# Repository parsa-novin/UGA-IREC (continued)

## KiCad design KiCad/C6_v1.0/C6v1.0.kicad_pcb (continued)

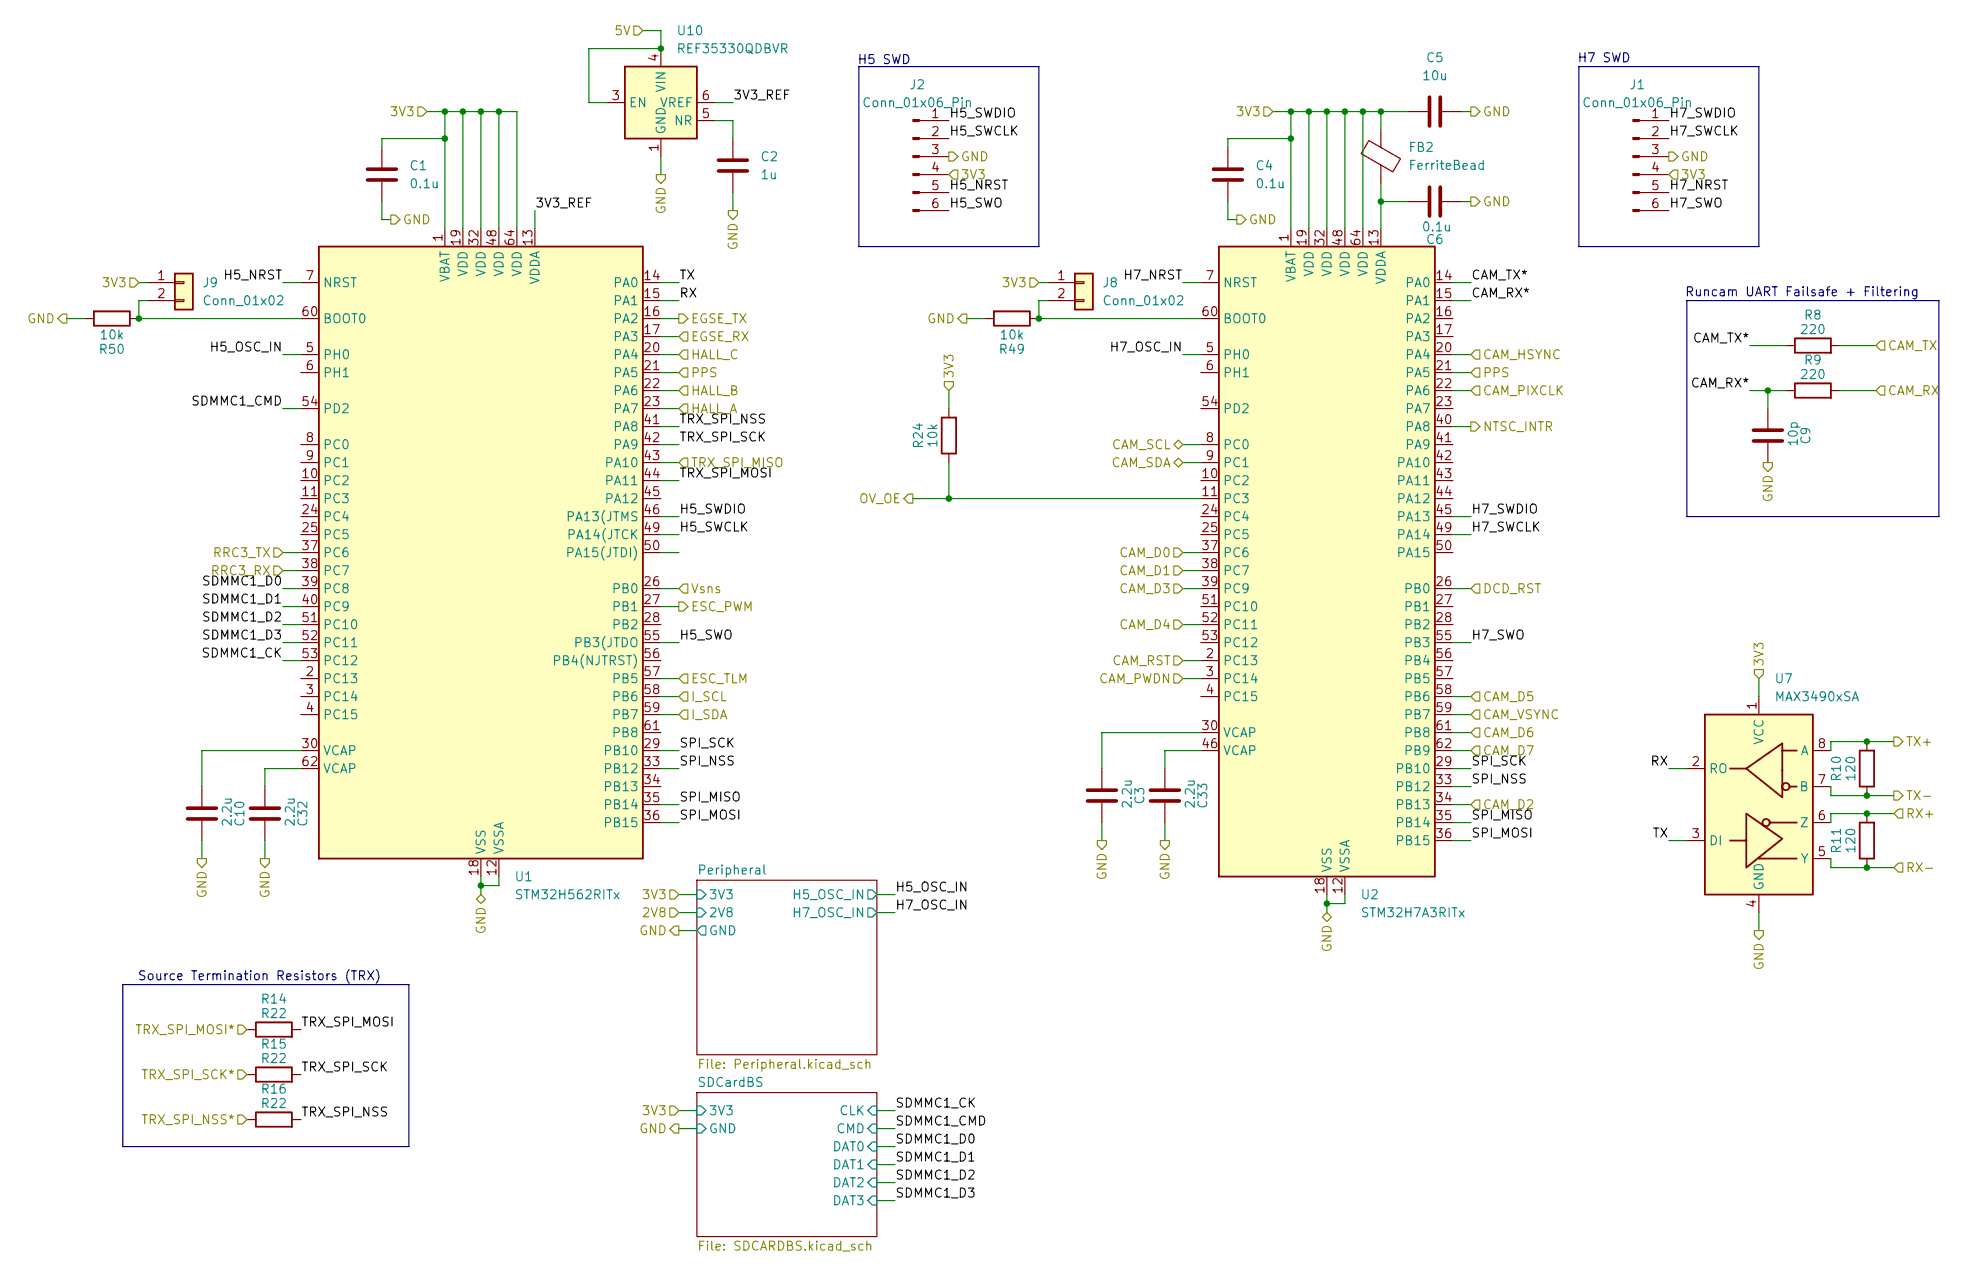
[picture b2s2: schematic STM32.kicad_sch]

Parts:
C1, C4, C6: 0.1u; C_0402_1005Metric_Pad0.74x0.62mm_HandSolder
C2: 1u; C_0402_1005Metric_Pad0.74x0.62mm_HandSolder
C3, C10, C32, C33: 2.2u; C_0402_1005Metric_Pad0.74x0.62mm_HandSolder
C5: 10u; C_0402_1005Metric_Pad0.74x0.62mm_HandSolder
C9: 10p; C_0402_1005Metric_Pad0.74x0.62mm_HandSolder
FB2: FerriteBead; R_0805_2012Metric
J1, J2: Conn_01x06_Pin; PinHeader_1x06_P2.54mm_Vertical
J8, J9: Conn_01x02; PinHeader_1x02_P2.54mm_Vertical
R8, R9: 220; R_0402_1005Metric_Pad0.72x0.64mm_HandSolder
R10, R11: 120; R_0402_1005Metric_Pad0.72x0.64mm_HandSolder
R14, R15, R16: R22; R_0402_1005Metric_Pad0.72x0.64mm_HandSolder
R24, R49, R50: 10k; R_0402_1005Metric_Pad0.72x0.64mm_HandSolder
U1: STM32H562RITx; LQFP-64_10x10mm_P0.5mm
U2: STM32H7A3RITx; LQFP-64_10x10mm_P0.5mm
U7: MAX3490xSA; SOIC-8_3.9x4.9mm_P1.27mm
U10: REF35330QDBVR; SOT-23-6

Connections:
/3V3: C1.2, C4.2, C5.2, FB2.1, J1.4, J2.4, J8.1, J9.1, R24.2, U1.1 (VBAT), U1.19 (VDD), U1.32 (VDD), U1.48 (VDD), U1.64 (VDD), U2.1 (VBAT), U2.19 (VDD), U2.32 (VDD), U2.48 (VDD), U2.64 (VDD), U7.1 (VCC); also elsewhere on the board
/5V: U10.3 (EN), U10.4 (VIN); also elsewhere on the board
/CAM_D0*: U2.37 (PC6); also elsewhere on the board
/CAM_D1*: U2.38 (PC7); also elsewhere on the board
/CAM_D2*: U2.34 (PB13); also elsewhere on the board
/CAM_D3*: U2.39 (PC9); also elsewhere on the board
/CAM_D4*: U2.52 (PC11); also elsewhere on the board
/CAM_D5*: U2.58 (PB6); also elsewhere on the board
/CAM_D6*: U2.61 (PB8); also elsewhere on the board
/CAM_D7*: U2.62 (PB9); also elsewhere on the board
/CAM_HSYNC*: U2.20 (PA4); also elsewhere on the board
/CAM_PCLK*: U2.22 (PA6); also elsewhere on the board
/CAM_PWDN*: U2.3 (PC14); also elsewhere on the board
/CAM_S: R24.1, U2.11 (PC3); also elsewhere on the board
/CAM_SCL: U2.8 (PC0); also elsewhere on the board
/CAM_SDA: U2.9 (PC1); also elsewhere on the board
/CAM_VSYNC*: U2.59 (PB7); also elsewhere on the board
/DCD_RST: U2.26 (PB0); also elsewhere on the board
/EGSE_RX: U1.17 (PA3); also elsewhere on the board
/EGSE_TX: U1.16 (PA2); also elsewhere on the board
/ESC_PWM: U1.27 (PB1); also elsewhere on the board
/ESC_TLM: U1.57 (PB5); also elsewhere on the board
/HALL_A: U1.23 (PA7); also elsewhere on the board
/HALL_B: U1.22 (PA6); also elsewhere on the board
/HALL_C: U1.20 (PA4); also elsewhere on the board
/I_SCL: U1.58 (PB6); also elsewhere on the board
/I_SDA: U1.59 (PB7); also elsewhere on the board
/NTSC_INTR: U2.40 (PA8); also elsewhere on the board
/OV_RST: U2.2 (PC13); also elsewhere on the board
/PPS: U1.21 (PA5), U2.21 (PA5); also elsewhere on the board
/RRC3_RX: U1.38 (PC7); also elsewhere on the board
/RRC3_TX: U1.37 (PC6); also elsewhere on the board
/RS422_RX+: R11.2, U7.6 (Z); also elsewhere on the board
/RS422_RX-: R11.1, U7.5 (Y); also elsewhere on the board
/RS422_TX+: R10.2, U7.8 (A); also elsewhere on the board
/RS422_TX-: R10.1, U7.7 (B); also elsewhere on the board
/SPLIT_RX: R9.2; also elsewhere on the board
/SPLIT_TX: R8.2; also elsewhere on the board
/STM32/3V3_REF: U1.13 (VDDA), U10.6 (VREF)
/STM32/CAM_RX*: C9.1, R9.1, U2.15 (PA1)
/STM32/CAM_TX*: R8.1, U2.14 (PA0)
/STM32/H5_NRST: J2.5, U1.7 (NRST)
/STM32/H5_OSC_IN: U1.5 (PH0); also elsewhere on the board
/STM32/H5_SWCLK: J2.2, U1.49 (PA14(JTCK)
/STM32/H5_SWDIO: J2.1, U1.46 (PA13(JTMS)
/STM32/H5_SWO: J2.6, U1.55 (PB3(JTDO)
/STM32/H7_NRST: J1.5, U2.7 (NRST)
/STM32/H7_OSC_IN: U2.5 (PH0); also elsewhere on the board
/STM32/H7_SWCLK: J1.2, U2.49 (PA14)
/STM32/H7_SWDIO: J1.1, U2.45 (PA13)
/STM32/H7_SWO: J1.6, U2.55 (PB3)
/STM32/RX: U1.15 (PA1), U7.2 (RO)
/STM32/SDMMC1_CK: U1.53 (PC12); also elsewhere on the board
/STM32/SDMMC1_CMD: U1.54 (PD2); also elsewhere on the board
/STM32/SDMMC1_D0: U1.39 (PC8); also elsewhere on the board
/STM32/SDMMC1_D1: U1.40 (PC9); also elsewhere on the board
/STM32/SDMMC1_D2: U1.51 (PC10); also elsewhere on the board
/STM32/SDMMC1_D3: U1.52 (PC11); also elsewhere on the board
/STM32/SPI_MISO: U1.35 (PB14), U2.35 (PB14)
/STM32/SPI_MOSI: U1.36 (PB15), U2.36 (PB15)
/STM32/SPI_NSS: U1.33 (PB12), U2.33 (PB12)
/STM32/SPI_SCK: U1.29 (PB10), U2.29 (PB10)
/STM32/TRX_SPI_MOSI: R14.2, U1.44 (PA11)
/STM32/TRX_SPI_NSS: R16.2, U1.41 (PA8)
/STM32/TRX_SPI_SCK: R15.2, U1.42 (PA9)
/STM32/TX: U1.14 (PA0), U7.3 (DI)
/TRX_MISO: U1.43 (PA10); also elsewhere on the board
/TRX_MOSI: R14.1; also elsewhere on the board
/TRX_NSS: R16.1; also elsewhere on the board
/TRX_SCK: R15.1; also elsewhere on the board
/Vsns: U1.26 (PB0); also elsewhere on the board
GND: C1.1, C2.1, C3.2, C4.1, C5.1, C6.1, C9.2, C10.2, C32.2, C33.2, J1.3, J2.3, R49.2, R50.2, U1.12 (VSSA), U1.18 (VSS), U1.31 (VSS), U1.47 (VSS), U1.63 (VSS), U2.12 (VSSA), U2.18 (VSS), U2.31 (VSS), U2.47 (VSS), U2.63 (VSS), U7.4 (GND), U10.1 (GND), U10.2 (GND); also elsewhere on the board
unnamed: C3.1, U2.30 (VCAP)
unnamed: C10.1, U1.30 (VCAP)
unnamed: C32.1, U1.62 (VCAP)
unnamed: C33.1, U2.46 (VCAP)
unnamed: J8.2, R49.1, U2.60 (BOOT0)
unnamed: J9.2, R50.1, U1.60 (BOOT0)
unnamed: C6.2, FB2.2, U2.13 (VDDA)
unnamed: C2.2, U10.5 (NR)

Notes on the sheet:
H7 SWD
Runcam UART Failsafe + Filtering
H5 SWD
Source Termination Resistors (TRX)

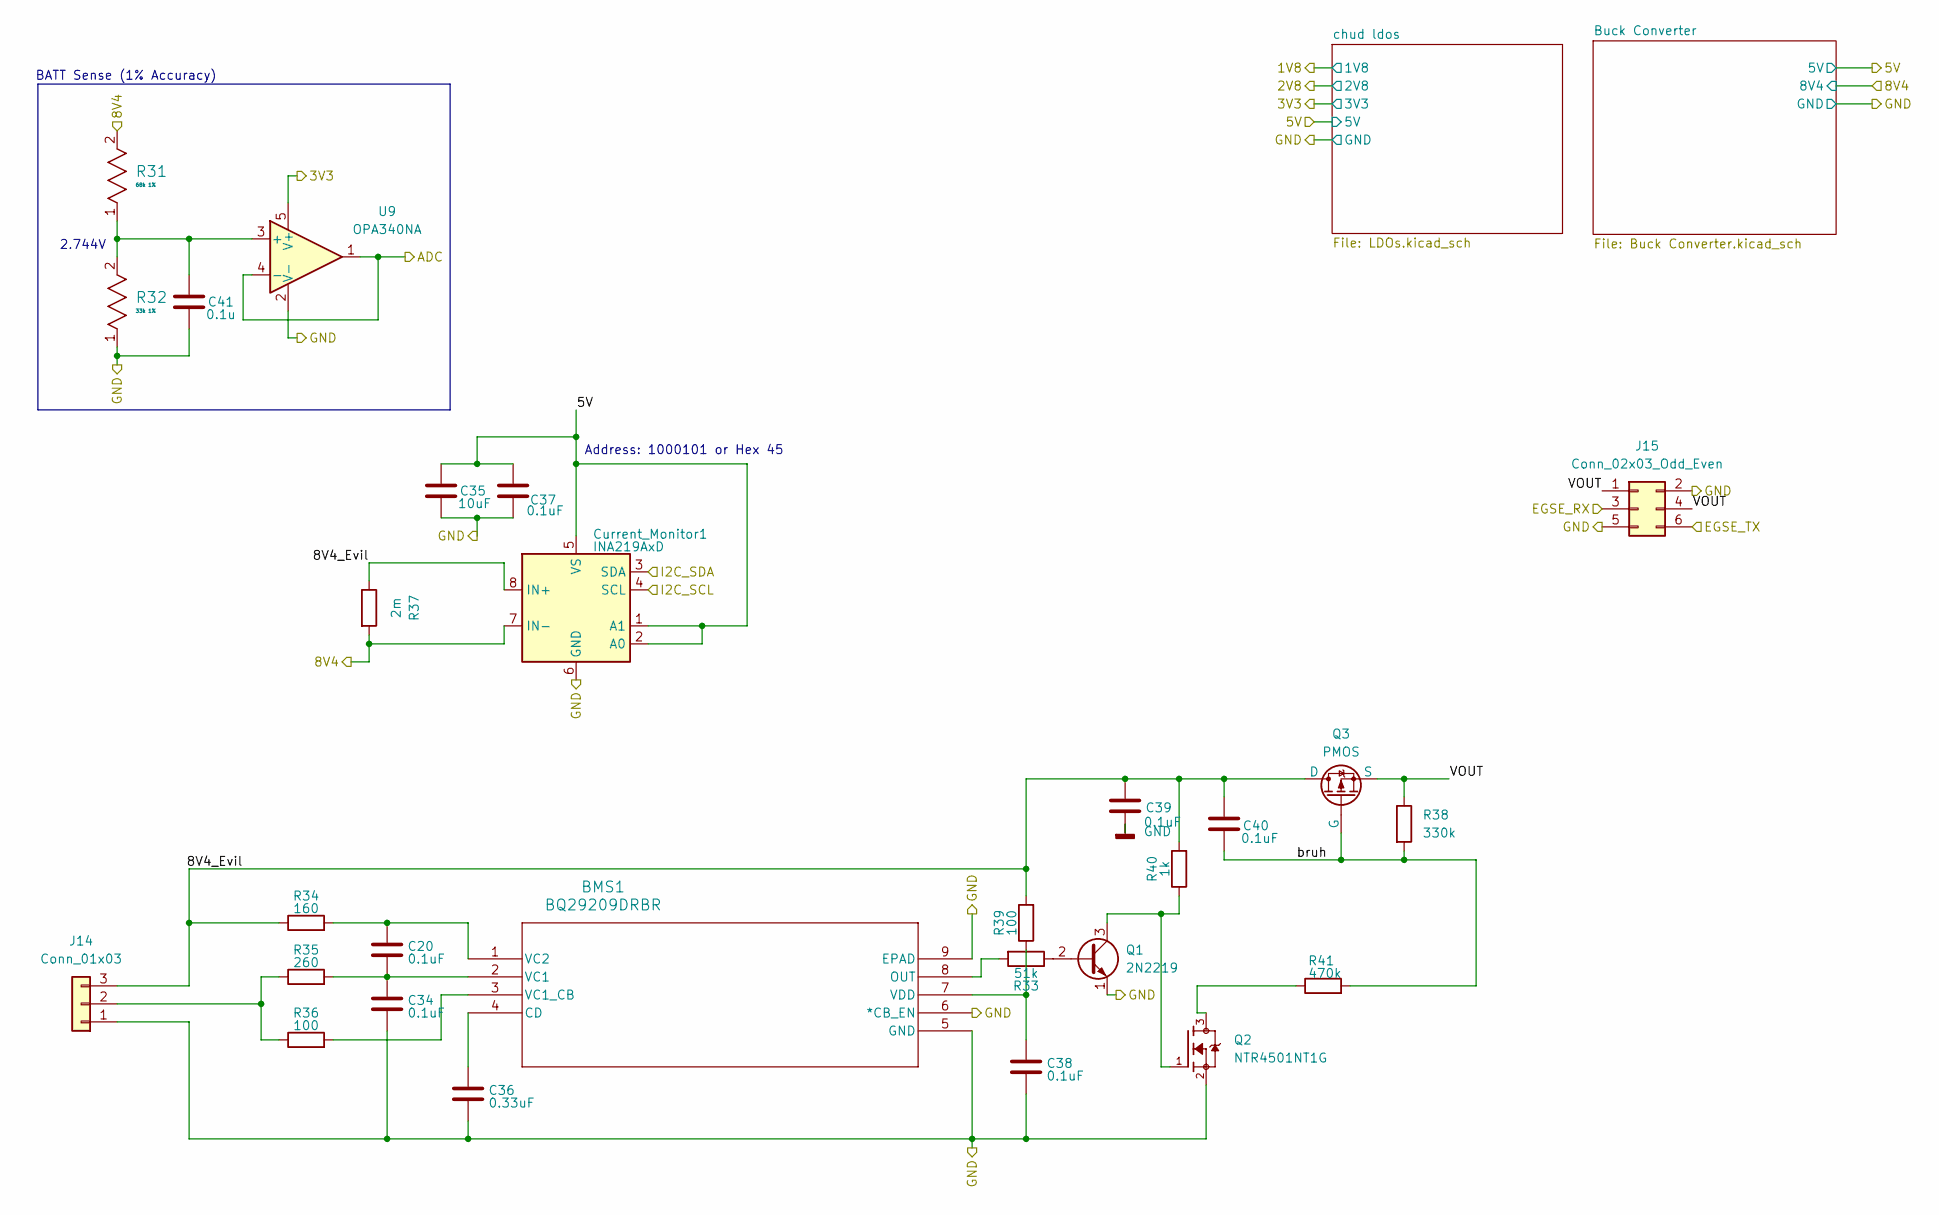
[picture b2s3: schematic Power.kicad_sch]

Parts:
BMS1: BQ29209DRBR; DRB8_1P6X2P4
C20, C34, C37, C38, C39, C40: 0.1uF; C_1206_3216Metric
C35: 10uF; C_1206_3216Metric
C36: 0.33uF; C_1206_3216Metric
C41: 0.1u; C_1206_3216Metric
Current_Monitor1: INA219AxD; SOIC-8_3.9x4.9mm_P1.27mm
J14: Conn_01x03; JST_XA_S03B-XASK-1_1x03_P2.50mm_Horizontal
J15: Conn_02x03_Odd_Even; CONN_SD-44764-001_06_MOL
Q1: 2N2219; TO-39-3
Q2: NTR4501NT1G; SOT95P237X111-3N; PARTREV 15
Q3: PMOS; SOT95P237X111-3N
R31: 68k 1%; R_0603_1608Metric_Pad0.98x0.95mm_HandSolder
R32: 33k 1%; R_0603_1608Metric_Pad0.98x0.95mm_HandSolder
R33: 51k; R_1206_3216Metric
R34: 160; R_1206_3216Metric
R35: 260; R_1206_3216Metric
R36, R39: 100; R_1206_3216Metric
R37: 2m; R_1206_3216Metric
R38: 330k; R_1206_3216Metric
R40: 1k; R_1206_3216Metric
R41: 470k; R_1206_3216Metric
U9: OPA340NA; SOT-23-5

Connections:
/3V3: U9.5 (V+); also elsewhere on the board
/5V: C35.1, C37.1, Current_Monitor1.1 (A1), Current_Monitor1.2 (A0), Current_Monitor1.5 (VS); also elsewhere on the board
/8V4: Current_Monitor1.7 (IN-), R31.2, R37.2; also elsewhere on the board
/EGSE_RX: J15.3; also elsewhere on the board
/EGSE_TX: J15.6; also elsewhere on the board
/I_SCL: Current_Monitor1.4 (SCL); also elsewhere on the board
/I_SDA: Current_Monitor1.3 (SDA); also elsewhere on the board
/Power/8V4_Evil: C39.1, C40.1, Current_Monitor1.8 (IN+), J14.3, Q3.1 (D), R34.1, R37.1, R39.2, R40.2
/Power/VOUT: J15.1, J15.4, Q3.3 (S), R38.1
/Power/bruh: C40.2, Q3.2 (G), R38.2, R41.2
/Vsns: U9.1, U9.4 (-); also elsewhere on the board
GND: BMS1.5 (GND), BMS1.6 (*CB_EN), BMS1.9 (EPAD), BMS1.V, C34.2, C35.2, C36.2, C37.2, C38.2, C39.2, C41.2, Current_Monitor1.6 (GND), J14.1, J15.2, J15.5, Q1.1 (E), Q2.2, R32.1, U9.2 (V-); also elsewhere on the board
unnamed: BMS1.4 (CD), C36.1
unnamed: BMS1.8 (OUT), R33.2
unnamed: BMS1.2 (VC1), C20.2, C34.1, R35.2
unnamed: BMS1.3 (VC1_CB), R36.2
unnamed: BMS1.1 (VC2), C20.1, R34.2
unnamed: BMS1.7 (VDD), C38.1, R39.1
unnamed: J14.2, R35.1, R36.1
unnamed: Q1.2 (B), R33.1
unnamed: Q1.3 (C), Q2.1, R40.1
unnamed: Q2.3, R41.1
unnamed: C41.1, R31.1, R32.2, U9.3 (+)

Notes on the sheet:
2.744V
Address: 1000101 or Hex 45
BATT Sense (1% Accuracy)

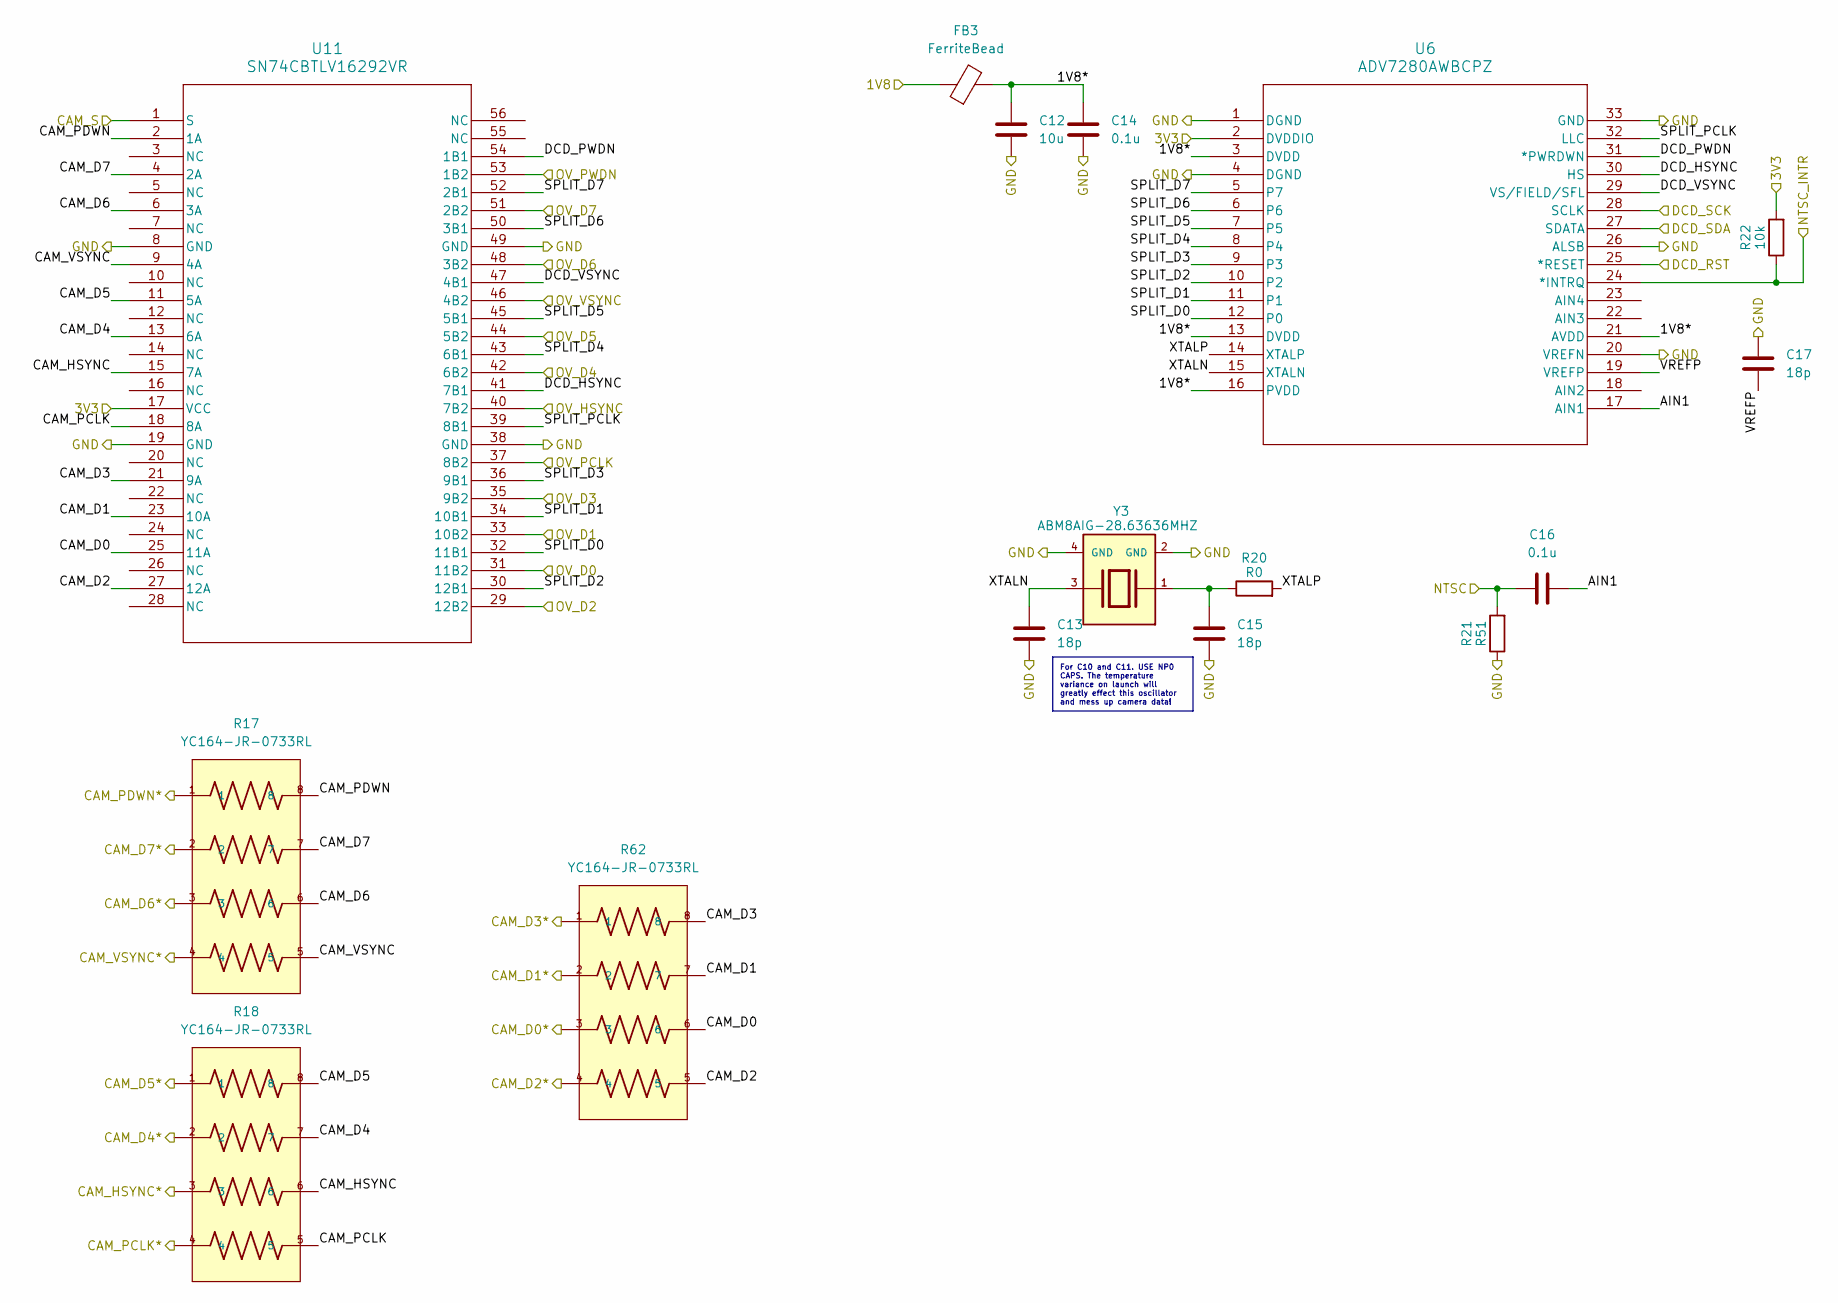
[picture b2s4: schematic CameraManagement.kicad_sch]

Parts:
C12: 10u; C_0402_1005Metric_Pad0.74x0.62mm_HandSolder
C13, C15, C17: 18p; C_0402_1005Metric_Pad0.74x0.62mm_HandSolder
C14, C16: 0.1u; C_0402_1005Metric_Pad0.74x0.62mm_HandSolder
FB3: FerriteBead; L_0201_0603Metric_Pad0.64x0.40mm_HandSolder
R17, R18, R62: YC164-JR-0733RL; RES_YC124_2X1_YAG-L; PARTREV 9
R20: R0; R_0402_1005Metric_Pad0.72x0.64mm_HandSolder
R21: R51; R_0402_1005Metric_Pad0.72x0.64mm_HandSolder
R22: 10k; R_0402_1005Metric_Pad0.72x0.64mm_HandSolder
U6: ADV7280AWBCPZ; CP-32-12_ADI-L
U11: SN74CBTLV16292VR; DGV56-L
Y3: ABM8AIG-28.63636MHZ; XTAL_ABM8AIG-28.63636MHZ-12-2Z-T3; PARTREV 43629

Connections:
/1V8: FB3.1; also elsewhere on the board
/3V3: R22.2, U6.2 (DVDDIO), U11.17 (VCC); also elsewhere on the board
/CAM_D0*: R62.3; also elsewhere on the board
/CAM_D1*: R62.2; also elsewhere on the board
/CAM_D2*: R62.4; also elsewhere on the board
/CAM_D3*: R62.1; also elsewhere on the board
/CAM_D4*: R18.2; also elsewhere on the board
/CAM_D5*: R18.1; also elsewhere on the board
/CAM_D6*: R17.3; also elsewhere on the board
/CAM_D7*: R17.2; also elsewhere on the board
/CAM_HSYNC*: R18.3; also elsewhere on the board
/CAM_PCLK*: R18.4; also elsewhere on the board
/CAM_PWDN*: R17.1; also elsewhere on the board
/CAM_S: U11.1 (S); also elsewhere on the board
/CAM_SCL: U6.28 (SCLK); also elsewhere on the board
/CAM_SDA: U6.27 (SDATA); also elsewhere on the board
/CAM_VSYNC*: R17.4; also elsewhere on the board
/CameraManagement/1V8*: C12.1, C14.1, FB3.2, U6.3 (DVDD), U6.13 (DVDD), U6.16 (PVDD), U6.21 (AVDD)
/CameraManagement/AIN1: C16.2, U6.17 (AIN1)
/CameraManagement/CAM_D0: R62.6, U11.25 (11A)
/CameraManagement/CAM_D1: R62.7, U11.23 (10A)
/CameraManagement/CAM_D2: R62.5, U11.27 (12A)
/CameraManagement/CAM_D3: R62.8, U11.21 (9A)
/CameraManagement/CAM_D4: R18.7, U11.13 (6A)
/CameraManagement/CAM_D5: R18.8, U11.11 (5A)
/CameraManagement/CAM_D6: R17.6, U11.6 (3A)
/CameraManagement/CAM_D7: R17.7, U11.4 (2A)
/CameraManagement/CAM_HSYNC: R18.6, U11.15 (7A)
/CameraManagement/CAM_PCLK: R18.5, U11.18 (8A)
/CameraManagement/CAM_PDWN: R17.8, U11.2 (1A)
/CameraManagement/CAM_VSYNC: R17.5, U11.9 (4A)
/CameraManagement/DCD_HSYNC: U6.30 (HS), U11.41 (7B1)
/CameraManagement/DCD_PWDN: U6.31 (*PWRDWN), U11.54 (1B1)
/CameraManagement/DCD_VSYNC: U6.29 (VS/FIELD/SFL), U11.47 (4B1)
/CameraManagement/SPLIT_D0: U6.12 (P0), U11.32 (11B1)
/CameraManagement/SPLIT_D1: U6.11 (P1), U11.34 (10B1)
/CameraManagement/SPLIT_D2: U6.10 (P2), U11.30 (12B1)
/CameraManagement/SPLIT_D3: U6.9 (P3), U11.36 (9B1)
/CameraManagement/SPLIT_D4: U6.8 (P4), U11.43 (6B1)
/CameraManagement/SPLIT_D5: U6.7 (P5), U11.45 (5B1)
/CameraManagement/SPLIT_D6: U6.6, U11.50 (3B1)
/CameraManagement/SPLIT_D7: U6.5 (P7), U11.52 (2B1)
/CameraManagement/SPLIT_PCLK: U6.32 (LLC), U11.39 (8B1)
/CameraManagement/VREFP: C17.2, U6.19 (VREFP)
/CameraManagement/XTALN: C13.1, U6.15 (XTALN), Y3.3
/CameraManagement/XTALP: R20.2, U6.14 (XTALP)
/DCD_RST: U6.25 (*RESET); also elsewhere on the board
/NTSC: C16.1, R21.2; also elsewhere on the board
/NTSC_INTR: R22.1, U6.24 (*INTRQ); also elsewhere on the board
/OV_D0: U11.31 (11B2); also elsewhere on the board
/OV_D1: U11.33 (10B2); also elsewhere on the board
/OV_D2: U11.29 (12B2); also elsewhere on the board
/OV_D3: U11.35 (9B2); also elsewhere on the board
/OV_D4: U11.42 (6B2); also elsewhere on the board
/OV_D5: U11.44 (5B2); also elsewhere on the board
/OV_D6: U11.48 (3B2); also elsewhere on the board
/OV_D7: U11.51 (2B2); also elsewhere on the board
/OV_HSYNC: U11.40 (7B2); also elsewhere on the board
/OV_PCLK: U11.37 (8B2); also elsewhere on the board
/OV_PWDN: U11.53 (1B2); also elsewhere on the board
/OV_VSYNC: U11.46 (4B2); also elsewhere on the board
GND: C12.2, C13.2, C14.2, C15.2, C17.1, R21.1, U6.1 (DGND), U6.4 (DGND), U6.20 (VREFN), U6.26 (ALSB), U6.33 (GND), U11.8 (GND), U11.19 (GND), U11.38 (GND), U11.49 (GND), Y3.2 (GND), Y3.4 (GND); also elsewhere on the board
unnamed: C15.1, R20.1, Y3.1

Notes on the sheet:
For C10 and C11. USE NP0 CAPS. The temperature variance on launch will greatly effect this oscillator and mess up camera data!

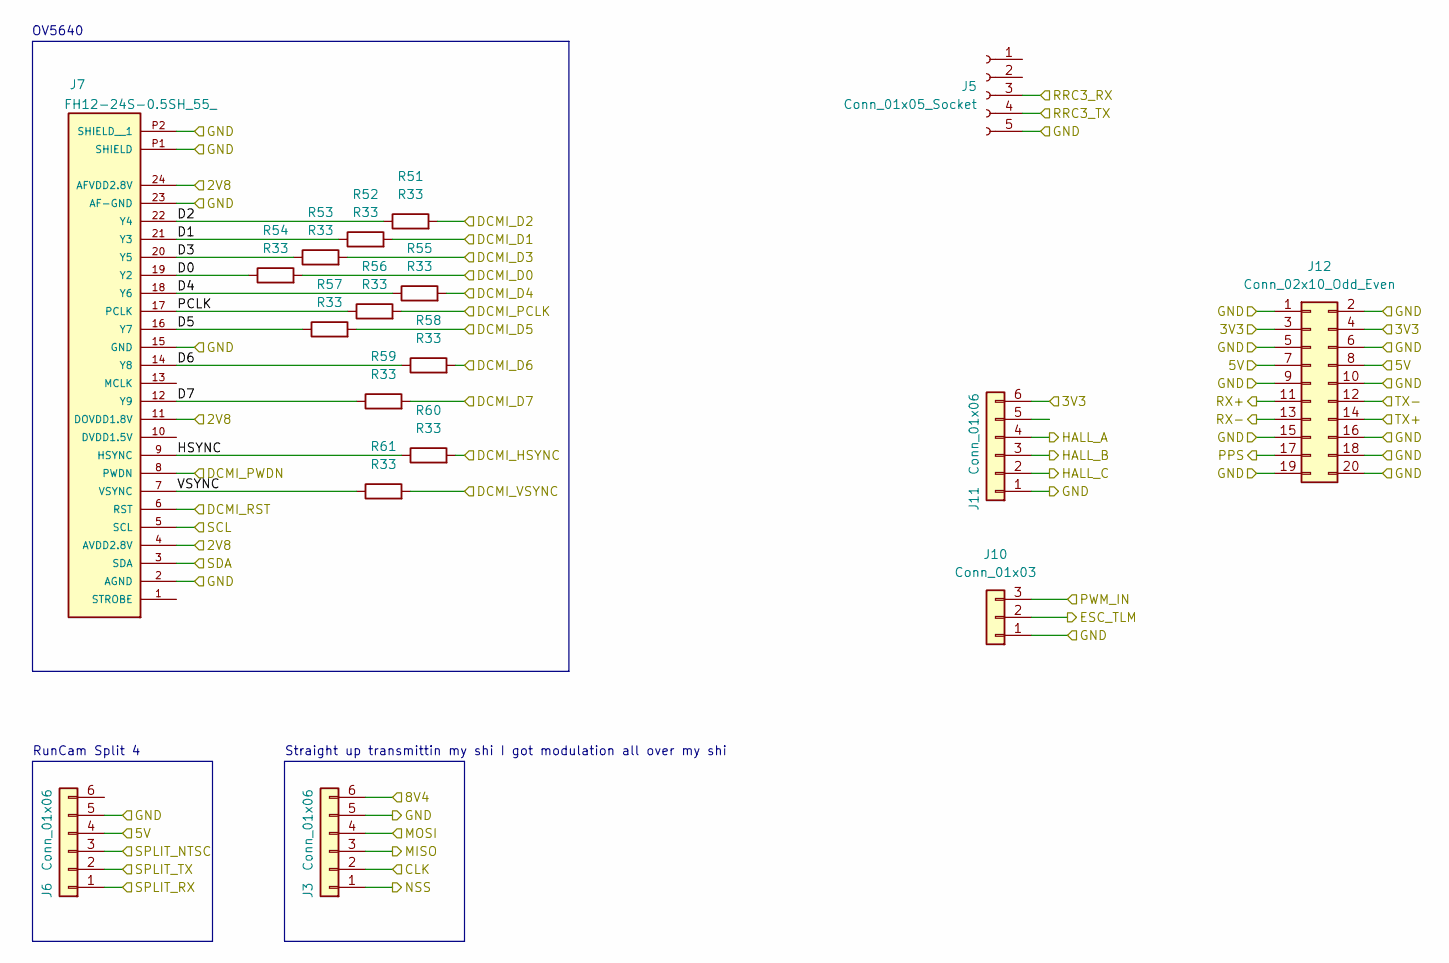
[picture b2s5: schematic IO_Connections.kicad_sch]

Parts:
J3, J6, J11: Conn_01x06; JST_XA_S06B-XASK-1_1x06_P2.50mm_Horizontal
J5: Conn_01x05_Socket; PinSocket_1x05_P2.00mm_Vertical
J7: FH12-24S-0.5SH_55_; CONN_FH12-22S-0.5SH55_HIR
J10: Conn_01x03; JST_XA_S03B-XASK-1_1x03_P2.50mm_Horizontal
J12: Conn_02x10_Odd_Even; PinHeader_2x10_P2.54mm_Vertical
R51, R52, R53, R54, R55, R56, R57, R58, R59, R60, R61: R33; R_0402_1005Metric_Pad0.72x0.64mm_HandSolder

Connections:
/2V8: J7.4 (AVDD2.8V), J7.11 (DOVDD1.8V), J7.24 (AFVDD2.8V); also elsewhere on the board
/3V3: J11.6, J12.3, J12.4; also elsewhere on the board
/5V: J6.4, J12.7, J12.8; also elsewhere on the board
/8V4: J3.6; also elsewhere on the board
/ESC_PWM: J10.3; also elsewhere on the board
/ESC_TLM: J10.2; also elsewhere on the board
/HALL_A: J11.4; also elsewhere on the board
/HALL_B: J11.3; also elsewhere on the board
/HALL_C: J11.2; also elsewhere on the board
/IO_Connections/D0: J7.19 (Y2), R54.1
/IO_Connections/D1: J7.21 (Y3), R52.1
/IO_Connections/D2: J7.22 (Y4), R51.1
/IO_Connections/D3: J7.20 (Y5), R53.1
/IO_Connections/D4: J7.18 (Y6), R55.1
/IO_Connections/D5: J7.16 (Y7), R57.1
/IO_Connections/D6: J7.14 (Y8), R58.1
/IO_Connections/D7: J7.12 (Y9), R59.1
/IO_Connections/HSYNC: J7.9 (HSYNC), R60.1
/IO_Connections/PCLK: J7.17 (PCLK), R56.1
/IO_Connections/VSYNC: J7.7 (VSYNC), R61.1
/NTSC: J6.3; also elsewhere on the board
/OV_D0: R54.2; also elsewhere on the board
/OV_D1: R52.2; also elsewhere on the board
/OV_D2: R51.2; also elsewhere on the board
/OV_D3: R53.2; also elsewhere on the board
/OV_D4: R55.2; also elsewhere on the board
/OV_D5: R57.2; also elsewhere on the board
/OV_D6: R58.2; also elsewhere on the board
/OV_D7: R59.2; also elsewhere on the board
/OV_HSYNC: R60.2; also elsewhere on the board
/OV_PCLK: R56.2; also elsewhere on the board
/OV_PWDN: J7.8 (PWDN); also elsewhere on the board
/OV_RST: J7.6 (RST); also elsewhere on the board
/OV_VSYNC: R61.2; also elsewhere on the board
/PPS: J12.17; also elsewhere on the board
/RRC3_RX: J5.3; also elsewhere on the board
/RRC3_TX: J5.4; also elsewhere on the board
/RS422_RX+: J12.11; also elsewhere on the board
/RS422_RX-: J12.13; also elsewhere on the board
/RS422_TX+: J12.14; also elsewhere on the board
/RS422_TX-: J12.12; also elsewhere on the board
/SCL: J7.5 (SCL); also elsewhere on the board
/SDA: J7.3 (SDA); also elsewhere on the board
/SPLIT_RX: J6.1; also elsewhere on the board
/SPLIT_TX: J6.2; also elsewhere on the board
/TRX_MISO: J3.3; also elsewhere on the board
/TRX_MOSI: J3.4; also elsewhere on the board
/TRX_NSS: J3.1; also elsewhere on the board
/TRX_SCK: J3.2; also elsewhere on the board
GND: J3.5, J5.5, J6.5, J7.2 (AGND), J7.15 (GND), J7.23 (AF-GND), J7.P1 (SHIELD), J7.P2 (SHIELD__1), J10.1, J11.1, J12.1, J12.2, J12.5, J12.6, J12.9, J12.10, J12.15, J12.16, J12.18, J12.19, J12.20; also elsewhere on the board

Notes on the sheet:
RunCam Split 4
Straight up transmittin my shi I got modulation all over my shi
OV5640

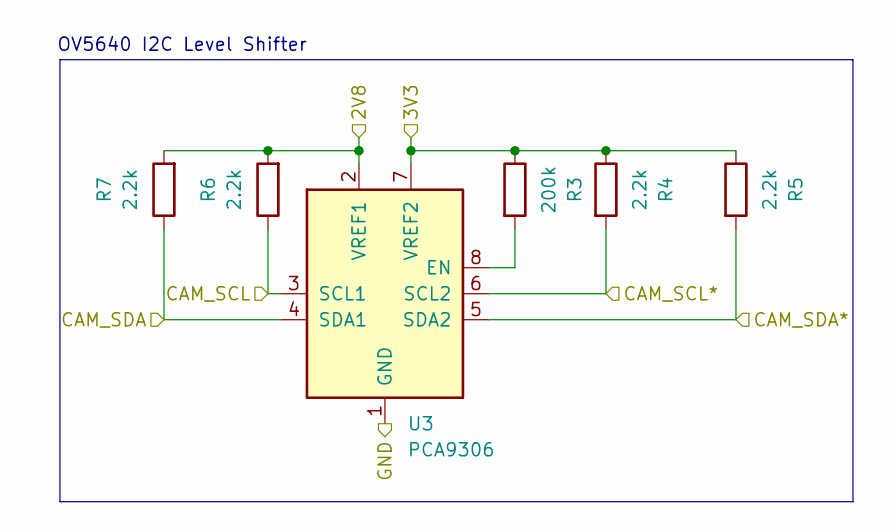
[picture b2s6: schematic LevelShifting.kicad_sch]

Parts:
R3: 200k; R_0402_1005Metric_Pad0.72x0.64mm_HandSolder
R4, R5, R6, R7: 2.2k; R_0402_1005Metric_Pad0.72x0.64mm_HandSolder
U3: PCA9306; SSOP-8_2.95x2.8mm_P0.65mm

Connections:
/2V8: R6.2, R7.2, U3.2 (VREF1); also elsewhere on the board
/3V3: R3.1, R4.1, R5.1, U3.7 (VREF2); also elsewhere on the board
/CAM_SCL: R4.2, U3.6 (SCL2); also elsewhere on the board
/CAM_SDA: R5.2, U3.5 (SDA2); also elsewhere on the board
/SCL: R6.1, U3.3 (SCL1); also elsewhere on the board
/SDA: R7.1, U3.4 (SDA1); also elsewhere on the board
GND: U3.1 (GND); also elsewhere on the board
unnamed: R3.2, U3.8 (EN)

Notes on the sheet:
OV5640 I2C Level Shifter

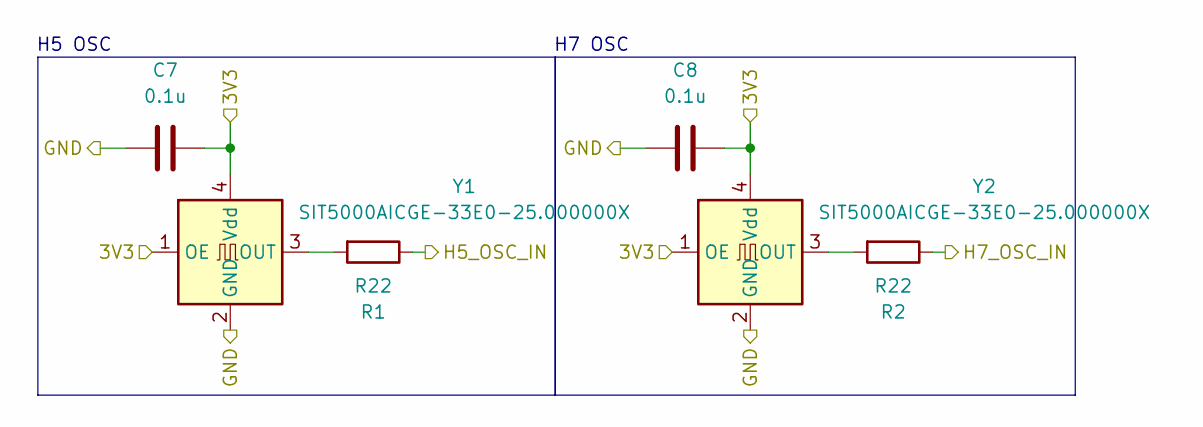
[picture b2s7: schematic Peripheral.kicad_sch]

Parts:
C7, C8: 0.1u; C_0402_1005Metric_Pad0.74x0.62mm_HandSolder
R1, R2: R22; R_0402_1005Metric_Pad0.72x0.64mm_HandSolder
Y1, Y2: SIT5000AICGE-33E0-25.000000X; Oscillator_SMD_SiT_PQFN-4Pin_5.0x3.2mm

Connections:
/3V3: C7.2, C8.2, Y1.1 (OE), Y1.4 (Vdd), Y2.1 (OE), Y2.4 (Vdd); also elsewhere on the board
/STM32/H5_OSC_IN: R1.1; also elsewhere on the board
/STM32/H7_OSC_IN: R2.1; also elsewhere on the board
GND: C7.1, C8.1, Y1.2 (GND), Y2.2 (GND); also elsewhere on the board
unnamed: R1.2, Y1.3 (OUT)
unnamed: R2.2, Y2.3 (OUT)

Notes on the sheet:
H7 OSC
H5 OSC

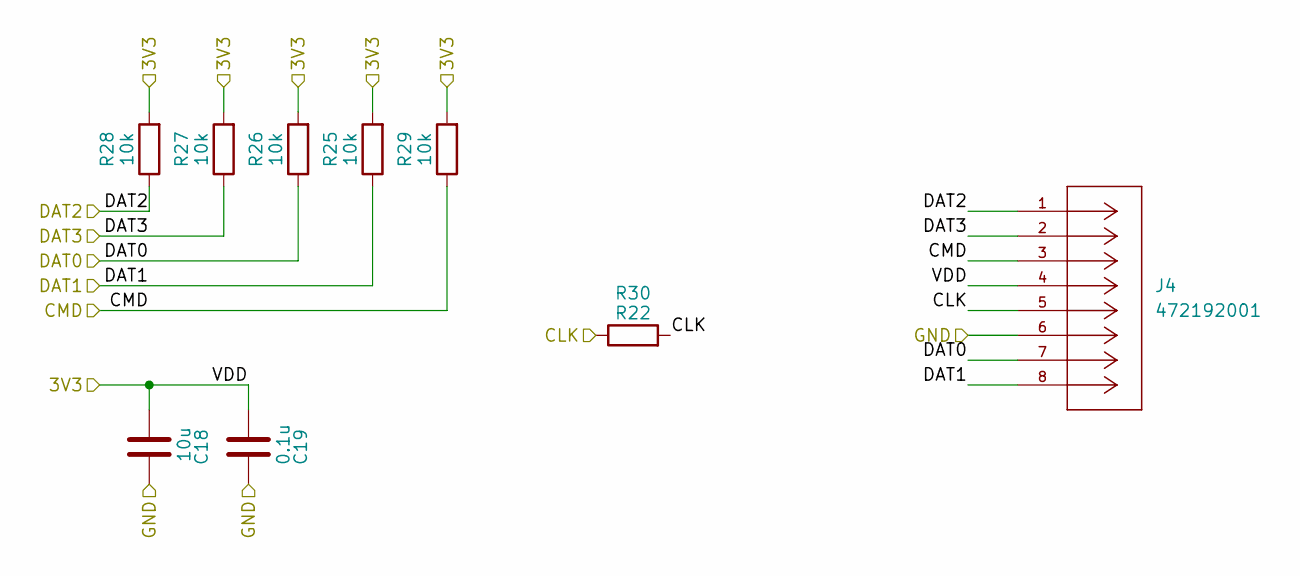
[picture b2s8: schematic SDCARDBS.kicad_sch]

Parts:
C18: 10u; C_0402_1005Metric_Pad0.74x0.62mm_HandSolder
C19: 0.1u; C_0402_1005Metric_Pad0.74x0.62mm_HandSolder
J4: 472192001; microSD_HC_Molex_47219-2001; MANUFACTURER_PART_NUMBER 472192001
R25, R26, R27, R28, R29: 10k; R_0402_1005Metric_Pad0.72x0.64mm_HandSolder
R30: R22; R_0402_1005Metric_Pad0.72x0.64mm_HandSolder

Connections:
/3V3: C18.1, C19.1, J4.4, R25.2, R26.2, R27.2, R28.2, R29.2; also elsewhere on the board
/STM32/SDMMC1_CK: J4.5, R30.1, R30.2; also elsewhere on the board
/STM32/SDMMC1_CMD: J4.3, R29.1; also elsewhere on the board
/STM32/SDMMC1_D0: J4.7, R26.1; also elsewhere on the board
/STM32/SDMMC1_D1: J4.8, R25.1; also elsewhere on the board
/STM32/SDMMC1_D2: J4.1, R28.1; also elsewhere on the board
/STM32/SDMMC1_D3: J4.2, R27.1; also elsewhere on the board
GND: C18.2, C19.2, J4.6; also elsewhere on the board

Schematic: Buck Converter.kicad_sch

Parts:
BUCKCONV1: TPS563200; SOT-23-6
C27, C28: CL31B106KAHNNNE/10uf; CAPC3216X180N
C29: 08053C104KAT2A/0.1uf; C_1206_3216Metric
C30, C31: CL10A226MP8NUNE/22uf; C_1206_3216Metric
J13: S02B-XASS-1LFSN; CONN2_S02B-XASS_295x496_JST
L1: SRN8040-3R3Y/3.3uH; L_Bourns-SRN8040_8x8.15mm
LED1: LTST-C190KRKT; LED_LTST-C190_LTO
R12: 40k; R_1206_3216Metric
R46: RC1206FR-07249RL/220ohm; R_1206_3216Metric
R47: RC0201FR-0756K2L/56.2K ohm; R_1206_3216Metric
R48: RC0201FR-0710KL/10kohm; R_1206_3216Metric

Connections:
/5V: C30.2, C31.2, L1.1, R46.2, R47.2; also elsewhere on the board
/8V4: BUCKCONV1.3 (VIN), C27.2, C28.2, J13.2; also elsewhere on the board
/Power/Buck Converter/buck-vbst_cap: BUCKCONV1.2 (SW), C29.2, L1.2
GND: BUCKCONV1.1 (GND), C27.1, C28.1, C30.1, C31.1, LED1.1, R12.2, R48.1; also elsewhere on the board
unnamed: BUCKCONV1.5 (EN), J13.1, R12.1
unnamed: BUCKCONV1.6 (VBST), C29.1
unnamed: BUCKCONV1.4 (VFB), R47.1, R48.2
unnamed: LED1.2, R46.1

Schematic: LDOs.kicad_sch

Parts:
1.8LDO1: LP5907MFX-1.8; SOT-23-5
2.8LDO1: LP5907MFX-2.8; SOT-23-5
C21, C22, C23, C24, C25, C26: CL10B105KP8NNNC 1uf; C_1206_3216Metric
LED2, LED3, LED4: LTST-C190KRKT; LED_LTST-C190_LTO
R42, R44: RC0805FR-07150RL; R_1206_3216Metric
R43: ERJ-2RKF1000X; R_1206_3216Metric
U8: TLV1117LV33DCYR; VREG_TLV1117LV33DCYR; PARTREV B

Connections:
/1V8: 1.8LDO1.5 (OUT), C24.2, R43.1; also elsewhere on the board
/2V8: 1.8LDO1.1 (IN), 1.8LDO1.3 (EN), 2.8LDO1.5 (OUT), C23.2, C25.2, R42.1; also elsewhere on the board
/3V3: 2.8LDO1.1 (IN), 2.8LDO1.3 (EN), C22.2, C26.2, R44.1, U8.2 (OUT_2), U8.4 (OUT_4); also elsewhere on the board
/5V: C21.2, U8.3 (IN); also elsewhere on the board
GND: 1.8LDO1.2 (GND), 2.8LDO1.2 (GND), C21.1, C22.1, C23.1, C24.1, C25.1, C26.1, LED2.1, LED3.1, LED4.1, U8.1 (GND); also elsewhere on the board
unnamed: LED2.2, R42.2
unnamed: LED3.2, R43.2
unnamed: LED4.2, R44.2
